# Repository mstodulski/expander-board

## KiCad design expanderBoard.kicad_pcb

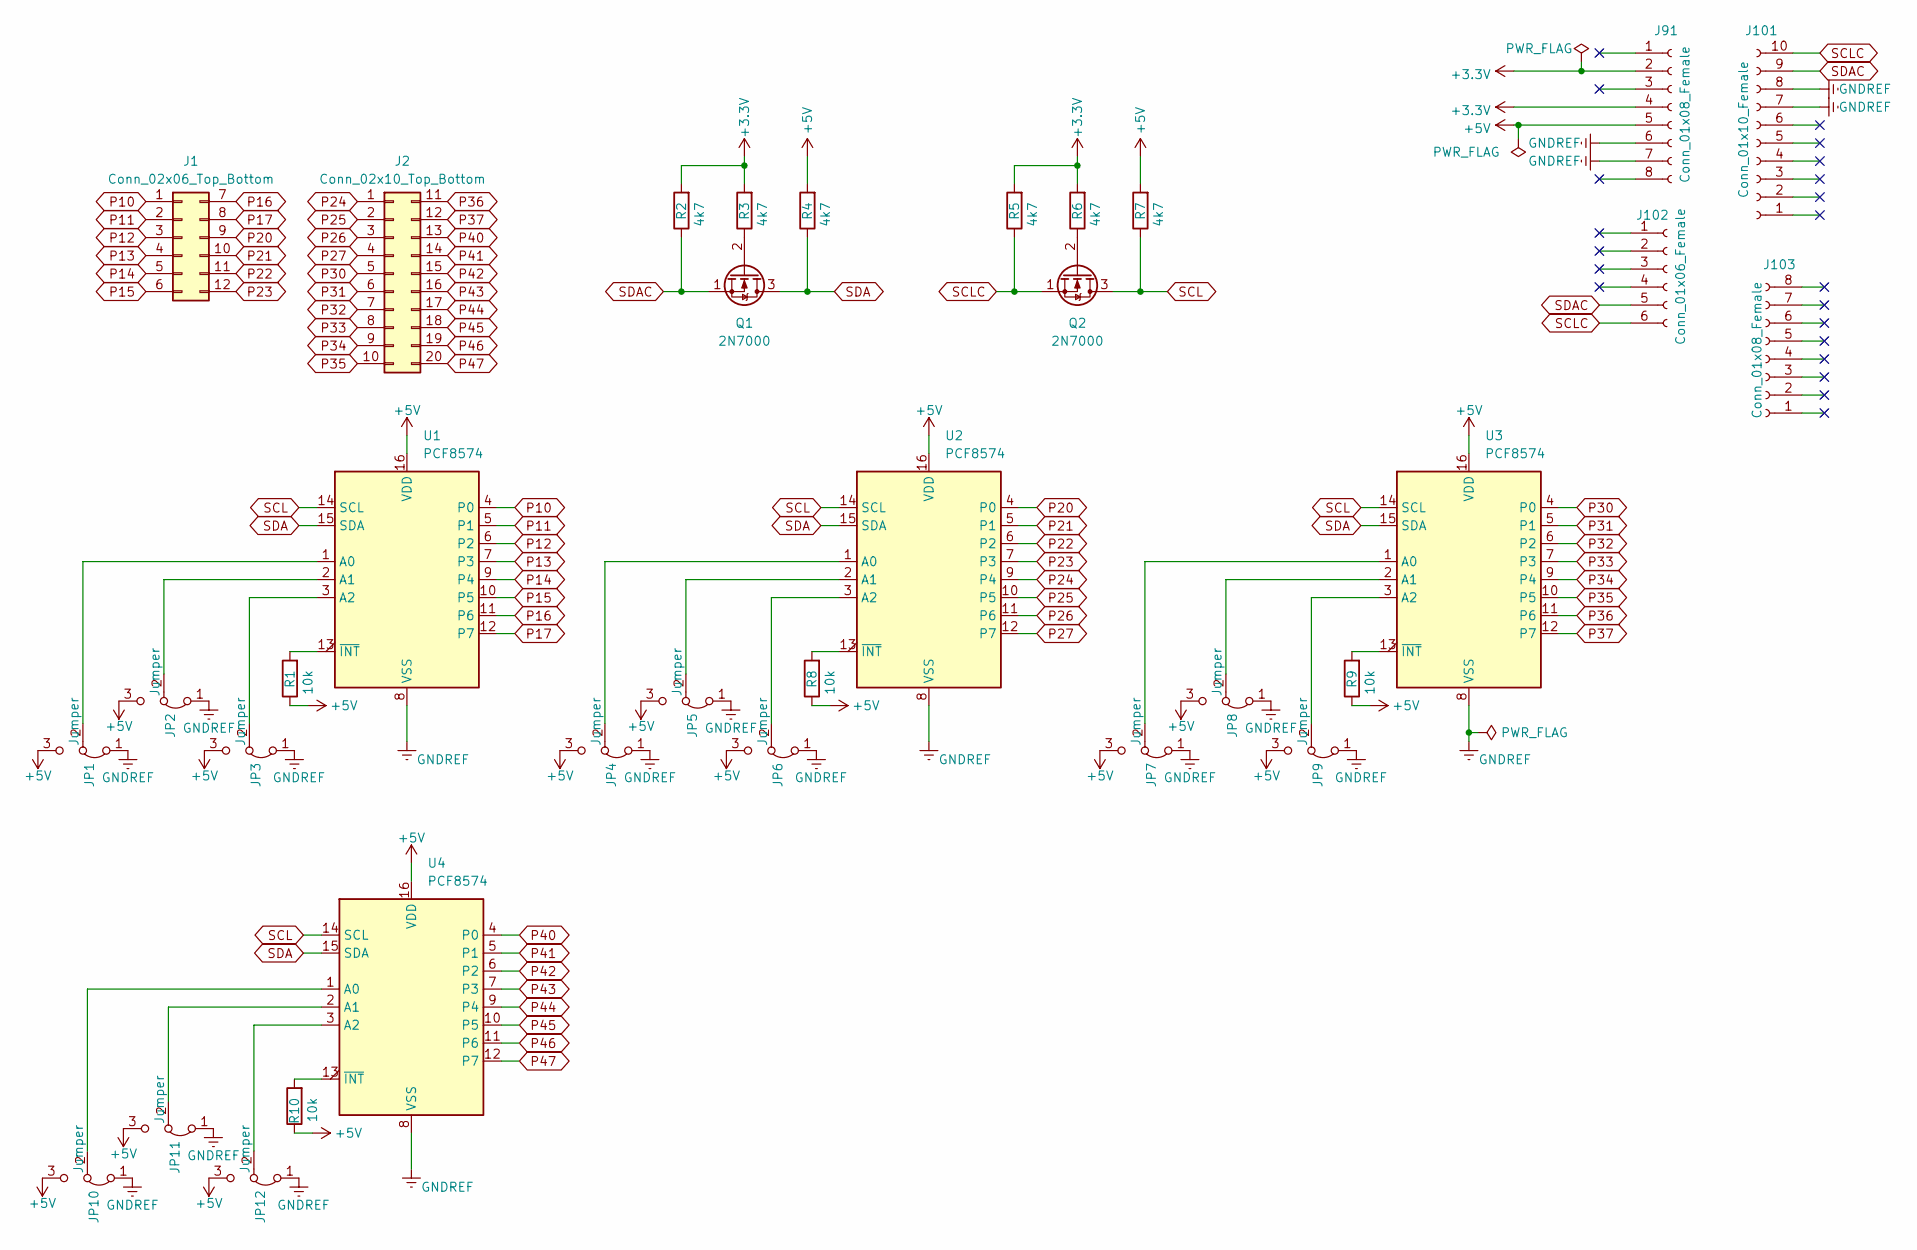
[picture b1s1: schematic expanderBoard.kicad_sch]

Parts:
J1: Conn_02x06_Top_Bottom; IDC-Header_2x06_P2.54mm_Horizontal
J2: Conn_02x10_Top_Bottom; IDC-Header_2x10_P2.54mm_Horizontal
J91, J103: Conn_01x08_Female; PinSocket_1x08_P2.54mm_Vertical
J101: Conn_01x10_Female; PinSocket_1x10_P2.54mm_Vertical
J102: Conn_01x06_Female; PinSocket_1x06_P2.54mm_Vertical
JP1, JP2, JP3, JP4, JP5, JP6, JP7, JP8, JP9, JP10, JP11, JP12: Jumper; PinHeader_1x03_P2.54mm_Vertical
Q1, Q2: 2N7000; TO-92_Inline_Wide
R1, R8, R9, R10: 10k; R_Axial_DIN0309_L9.0mm_D3.2mm_P2.54mm_Vertical
R2, R3, R4, R5, R6, R7: 4k7; R_Axial_DIN0309_L9.0mm_D3.2mm_P2.54mm_Vertical
U1, U2, U3, U4: PCF8574; DIP-16_W7.62mm_Socket

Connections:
+3.3V: J91.2, J91.4, R2.2, R3.2, R5.2, R6.2
+5V: J91.5, JP1.3 (B), JP2.3 (B), JP3.3 (B), JP4.3 (B), JP5.3 (B), JP6.3 (B), JP7.3 (B), JP8.3 (B), JP9.3 (B), JP10.3 (B), JP11.3 (B), JP12.3 (B), R1.1, R4.2, R7.2, R8.1, R9.1, R10.1, U1.16 (VDD), U2.16 (VDD), U3.16 (VDD), U4.16 (VDD)
GNDREF: J91.6, J91.7, J101.7, J101.8, JP1.1 (A), JP2.1 (A), JP3.1 (A), JP4.1 (A), JP5.1 (A), JP6.1 (A), JP7.1 (A), JP8.1 (A), JP9.1 (A), JP10.1 (A), JP11.1 (A), JP12.1 (A), U1.8 (VSS), U2.8 (VSS), U3.8 (VSS), U4.8 (VSS)
unnamed: JP1.2 (C), U1.1 (A0)
unnamed: JP2.2 (C), U1.2 (A1)
unnamed: JP3.2 (C), U1.3 (A2)
unnamed: JP4.2 (C), U2.1 (A0)
unnamed: JP5.2 (C), U2.2 (A1)
unnamed: JP6.2 (C), U2.3 (A2)
unnamed: JP7.2 (C), U3.1 (A0)
unnamed: JP8.2 (C), U3.2 (A1)
unnamed: JP9.2 (C), U3.3 (A2)
unnamed: JP10.2 (C), U4.1 (A0)
unnamed: JP11.2 (C), U4.2 (A1)
unnamed: JP12.2 (C), U4.3 (A2)
unnamed: Q1.2 (G), R3.1
unnamed: Q2.2 (G), R6.1
unnamed: R1.2, U1.13 (~INT)
unnamed: R8.2, U2.13 (~INT)
unnamed: R9.2, U3.13 (~INT)
unnamed: R10.2, U4.13 (~INT)
P10: J1.1, U1.4 (P0)
P11: J1.2, U1.5 (P1)
P12: J1.3, U1.6 (P2)
P13: J1.4, U1.7 (P3)
P14: J1.5, U1.9 (P4)
P15: J1.6, U1.10 (P5)
P16: J1.7, U1.11 (P6)
P17: J1.8, U1.12 (P7)
P20: J1.9, U2.4 (P0)
P21: J1.10, U2.5 (P1)
P22: J1.11, U2.6 (P2)
P23: J1.12, U2.7 (P3)
P24: J2.1, U2.9 (P4)
P25: J2.2, U2.10 (P5)
P26: J2.3, U2.11 (P6)
P27: J2.4, U2.12 (P7)
P30: J2.5, U3.4 (P0)
P31: J2.6, U3.5 (P1)
P32: J2.7, U3.6 (P2)
P33: J2.8, U3.7 (P3)
P34: J2.9, U3.9 (P4)
P35: J2.10, U3.10 (P5)
P36: J2.11, U3.11 (P6)
P37: J2.12, U3.12 (P7)
P40: J2.13, U4.4 (P0)
P41: J2.14, U4.5 (P1)
P42: J2.15, U4.6 (P2)
P43: J2.16, U4.7 (P3)
P44: J2.17, U4.9 (P4)
P45: J2.18, U4.10 (P5)
P46: J2.19, U4.11 (P6)
P47: J2.20, U4.12 (P7)
SCL: Q2.3 (D), R7.1, U1.14 (SCL), U2.14 (SCL), U3.14 (SCL), U4.14 (SCL)
SCLC: J101.10, J102.6, Q2.1 (S), R5.1
SDA: Q1.3 (D), R4.1, U1.15 (SDA), U2.15 (SDA), U3.15 (SDA), U4.15 (SDA)
SDAC: J101.9, J102.5, Q1.1 (S), R2.1

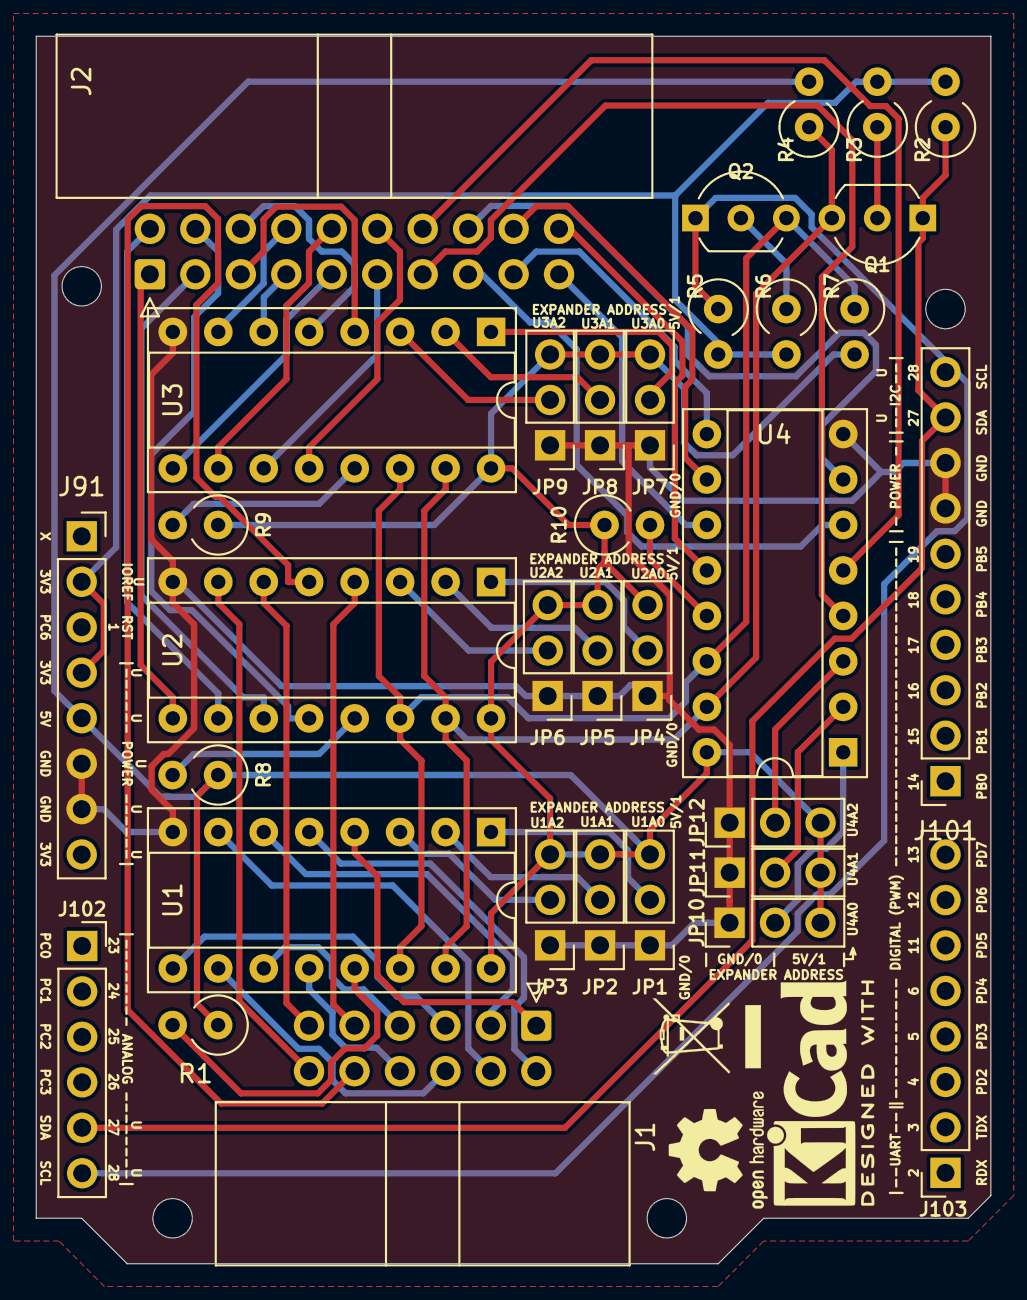
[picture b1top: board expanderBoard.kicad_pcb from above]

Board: 2 copper layers, 53.3 x 68.6 mm, 37 parts (0 on the bottom side), 57 nets.

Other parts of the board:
REF997: WEEE-Logo_4.2x6mm_SilkScreen
REF998: KiCad-Logo2_5mm_SilkScreen
REF999: OSHW-Logo2_7.3x6mm_SilkScreen

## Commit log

2024-04-19 add renders
